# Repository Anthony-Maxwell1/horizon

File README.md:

# Horizon

## AI Usage

AI was used during the schematic stage, providing insight on component suggestions, finding some obscure docs and providing wiring/gpio usage suggestions. It was also used to review the schematic, in quick prototyping stage. It was also used quite heavily in understanding concepts such as decoupling, and pretty heavily in instructing on how to apply decoupling.

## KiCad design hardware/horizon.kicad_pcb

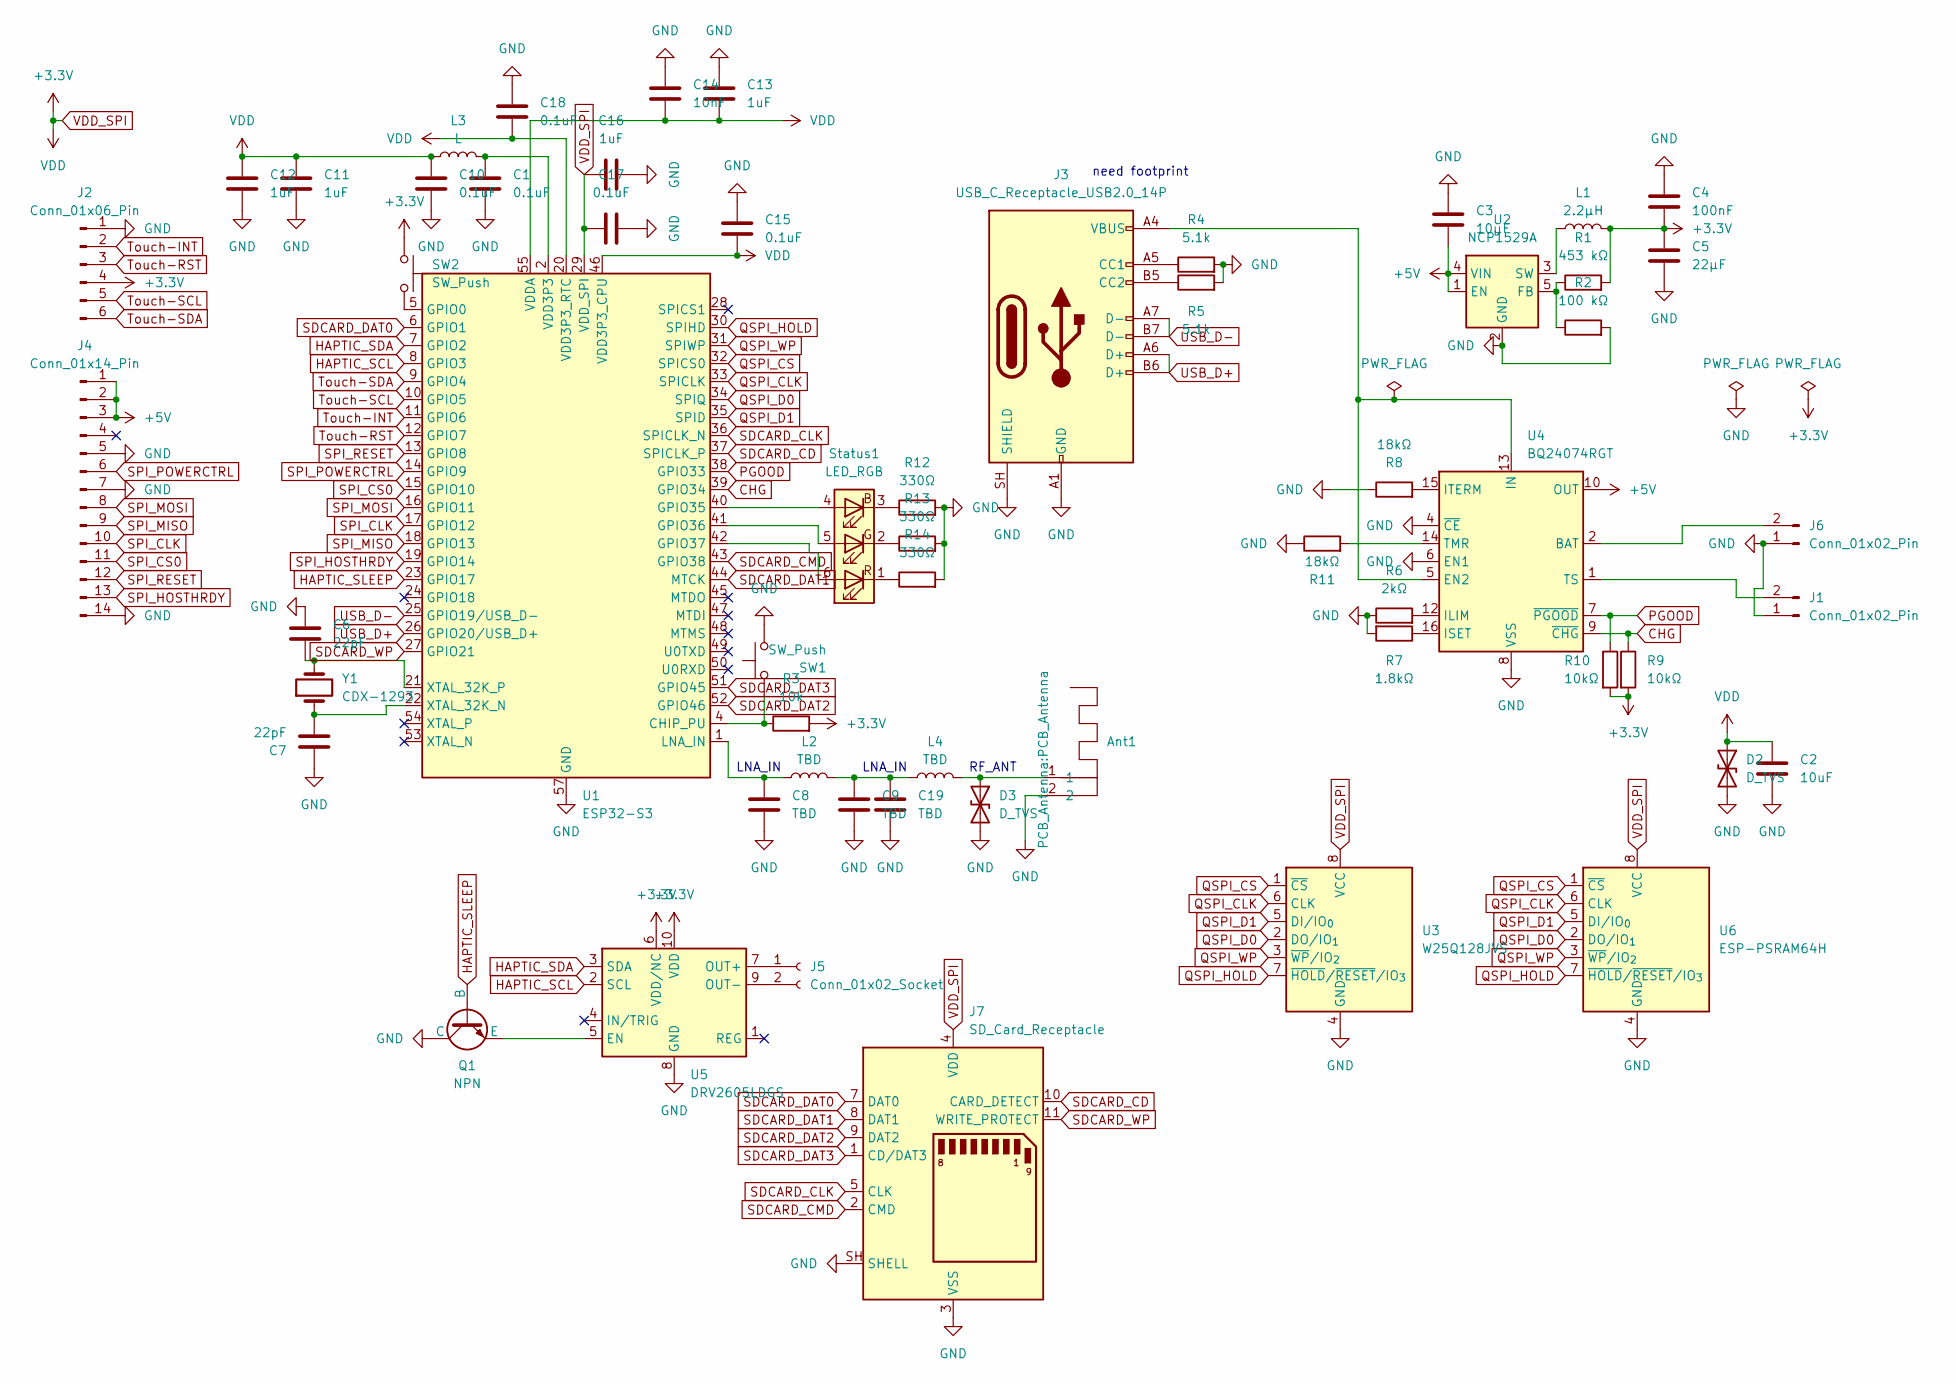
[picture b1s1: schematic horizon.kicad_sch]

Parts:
Ant1: PCB_Antenna:PCB_Antenna; PCB_Antenna
C1: 0.1uF; D_0402_1005Metric
C2: 10uF; C_0201_0603Metric
C3: 10µF; C_0201_0603Metric
C4: 100nF; C_0201_0603Metric
C5: 22µF; C_0201_0603Metric
C6, C7: 22pF; C_0201_0603Metric
C8, C9, C19: TBD; C_0201_0603Metric
C10, C15, C17, C18: 0.1uF; C_0201_0603Metric
C11, C12, C13, C16: 1uF; C_0201_0603Metric
C14: 10nF; C_0201_0603Metric
D2, D3: D_TVS; D_0402_1005Metric
J1, J6: Conn_01x02_Pin; JST_PH_S2B-PH-K_1x02_P2.00mm_Horizontal
J2: Conn_01x06_Pin; Hirose_FH12-6S-0.5SH_1x06-1MP_P0.50mm_Horizontal
J3: USB_C_Receptacle_USB2.0_14P; USB_C_Receptacle_HRO_TYPE-C-31-M-12
J4: Conn_01x14_Pin; Hirose_FH12-14S-0.5SH_1x14-1MP_P0.50mm_Horizontal
J5: Conn_01x02_Socket; 2x solder pads
J7: SD_Card_Receptacle; SD_TE_2041021
L1: 2.2µH; L_Bourns_SDR0604
L2, L4: TBD; L_Bourns_SDR0604
L3: L; L_Bourns_SDR0604
Q1: NPN; TO-92L
R1: 453 kΩ; R_0603_1608Metric
R2: 100 kΩ; R_0603_1608Metric
R3: 10k; R_0603_1608Metric
R4, R5: 5.1k; R_0603_1608Metric
R6: 2kΩ; R_0603_1608Metric
R7: 1.8kΩ; R_0603_1608Metric
R8, R11: 18kΩ; R_0603_1608Metric
R9, R10: 10kΩ; R_0603_1608Metric
R12, R13, R14: 330Ω; R_0603_1608Metric
SW1: SW_Push; SW_PUSH_6mm
SW2: SW_Push; SW_Push_1P2T_Vertical_E-Switch_800UDP8P1A1M6
Status1: LED_RGB; LED_RGB_5050-6
U1: ESP32-S3; QFN-56-1EP_7x7mm_P0.4mm_EP4x4mm
U2: NCP1529A; SOT-23-5
U3: W25Q128JVS; SOIC-8_5.3x5.3mm_P1.27mm
U4: BQ24074RGT; VQFN-16-1EP_3x3mm_P0.5mm_EP1.6x1.6mm
U5: DRV2605LDGS; TSSOP-10_3x3mm_P0.5mm
U6: ESP-PSRAM64H; SOIC-8_5.3x5.3mm_P1.27mm
Y1: CDX-1293; Crystal_SMD_3215-2Pin_3.2x1.5mm

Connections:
+5V: C3.1, J4.1, J4.2, J4.3, U2.1 (EN), U2.4 (VIN), U4.10 (OUT), U4.11 (OUT)
CHG: R9.1, U1.39 (GPIO34), U4.9 (~CHG)
GND: Ant1.2, C1.2, C2.2, C3.2, C4.2, C5.2, C6.2, C7.2, C8.2, C9.2, C10.2, C11.2, C12.2, C13.2, C14.2, C15.2, C16.2, C17.2, C18.2, C19.2, D2.2 (A2), D3.2 (A2), J1.1, J2.1, J3.A1 (GND), J3.A12 (GND), J3.B1 (GND), J3.B12 (GND), J3.SH (SHIELD), J4.5, J4.7, J4.14, J6.1, J7.3 (VSS), J7.6 (VSS), J7.SH (SHELL), Q1.1 (C), R2.2, R4.2, R5.2, R6.1, R7.2, R8.1, R11.1, R12.2, R13.2, R14.2, SW1.2, U1.57 (GND), U2.2 (GND), U3.4 (GND), U4.4 (~CE), U4.6 (EN1), U4.8 (VSS), U4.17 (VSS), U5.8 (GND), U6.4 (GND)
HAPTIC_SCL: U1.8 (GPIO3), U5.2 (SCL)
HAPTIC_SDA: U1.7 (GPIO2), U5.3 (SDA)
HAPTIC_SLEEP: Q1.2 (B), U1.23 (GPIO17)
unnamed: C1.1, L3.2, U1.2 (VDD3P3), U1.3 (VDD3P3)
unnamed: C9.1, C19.1, L2.2, L4.1
unnamed: Ant1.1, D3.1 (A1), L4.2
unnamed: J1.2, U4.1 (TS)
unnamed: J3.A5 (CC1), R4.1
unnamed: J3.B5 (CC2), R5.1
unnamed: J5.1, U5.7 (OUT+)
unnamed: J5.2, U5.9 (OUT-)
unnamed: J6.2, U4.2 (BAT), U4.3 (BAT)
unnamed: Q1.3 (E), U5.5 (EN)
unnamed: Status1.4 (BA), U1.40 (GPIO35)
unnamed: R12.1, Status1.3 (BK)
unnamed: Status1.5 (GA), U1.41 (GPIO36)
unnamed: R13.1, Status1.2 (GK)
unnamed: Status1.6 (RA), U1.42 (GPIO37)
unnamed: R14.1, Status1.1 (RK)
unnamed: R3.1, SW1.1, U1.4 (CHIP_PU)
unnamed: SW2.2, U1.5 (GPIO0)
unnamed: C8.1, L2.1, U1.1 (LNA_IN)
unnamed: C7.1, U1.22 (XTAL_32K_N), Y1.1
unnamed: C6.1, U1.21 (XTAL_32K_P), Y1.2
unnamed: R1.1, R2.1, U2.5 (FB)
unnamed: L1.1, U2.3 (SW)
unnamed: J3.A4 (VBUS), J3.A9 (VBUS), J3.B4 (VBUS), J3.B9 (VBUS), U4.5 (EN2), U4.13 (IN)
unnamed: R6.2, U4.12 (ILIM)
unnamed: R7.1, U4.16 (ISET)
unnamed: R8.2, U4.15 (ITERM)
unnamed: R11.2, U4.14 (TMR)
PGOOD: R10.1, U1.38 (GPIO33), U4.7 (~PGOOD)
QSPI_CLK: U1.33 (SPICLK), U3.6 (CLK), U6.6 (CLK)
QSPI_CS: U1.32 (SPICS0), U3.1 (~CS), U6.1 (~CS)
QSPI_D0: U1.34 (SPIQ), U3.2 (DO/IO_{1}), U6.2 (DO/IO_{1})
QSPI_D1: U1.35 (SPID), U3.5 (DI/IO_{0}), U6.5 (DI/IO_{0})
QSPI_HOLD: U1.30 (SPIHD), U3.7 (~HOLD/~RESET/IO_{3}), U6.7 (~HOLD/~RESET/IO_{3})
QSPI_WP: U1.31 (SPIWP), U3.3 (~WP/IO_{2}), U6.3 (~WP/IO_{2})
SDCARD_CD: J7.10 (CARD_DETECT), U1.37 (SPICLK_P)
SDCARD_CLK: J7.5 (CLK), U1.36 (SPICLK_N)
SDCARD_CMD: J7.2 (CMD), U1.43 (GPIO38)
SDCARD_DAT0: J7.7 (DAT0), U1.6 (GPIO1)
SDCARD_DAT1: J7.8 (DAT1), U1.44 (MTCK)
SDCARD_DAT2: J7.9 (DAT2), U1.52 (GPIO46)
SDCARD_DAT3: J7.1 (CD/DAT3), U1.51 (GPIO45)
SDCARD_WP: J7.11 (WRITE_PROTECT), U1.27 (GPIO21)
SPI_CLK: J4.10, U1.17 (GPIO12)
SPI_CS0: J4.11, U1.15 (GPIO10)
SPI_HOSTHRDY: J4.13, U1.19 (GPIO14)
SPI_MISO: J4.9, U1.18 (GPIO13)
SPI_MOSI: J4.8, U1.16 (GPIO11)
SPI_POWERCTRL: J4.6, U1.14 (GPIO9)
SPI_RESET: J4.12, U1.13 (GPIO8)
Touch-INT: J2.2, U1.11 (GPIO6)
Touch-RST: J2.3, U1.12 (GPIO7)
Touch-SCL: J2.5, U1.10 (GPIO5)
Touch-SDA: J2.6, U1.9 (GPIO4)
USB_D+: J3.A6 (D+), J3.B6 (D+), U1.26 (GPIO20/USB_D+)
USB_D-: J3.A7 (D-), J3.B7 (D-), U1.25 (GPIO19/USB_D-)
VDD_SPI: C2.1, C4.1, C5.1, C10.1, C11.1, C12.1, C13.1, C14.1, C15.1, C16.1, C17.1, C18.1, D2.1 (A1), J2.4, J7.4 (VDD), L1.2, L3.1, R1.2, R3.2, R9.2, R10.2, SW2.1, U1.20 (VDD3P3_RTC), U1.29 (VDD_SPI), U1.46 (VDD3P3_CPU), U1.55 (VDDA), U1.56 (VDDA), U3.8 (VCC), U5.6 (VDD/NC), U5.10 (VDD), U6.8 (VCC)

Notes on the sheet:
LNA_IN
need footprint
RF_ANT

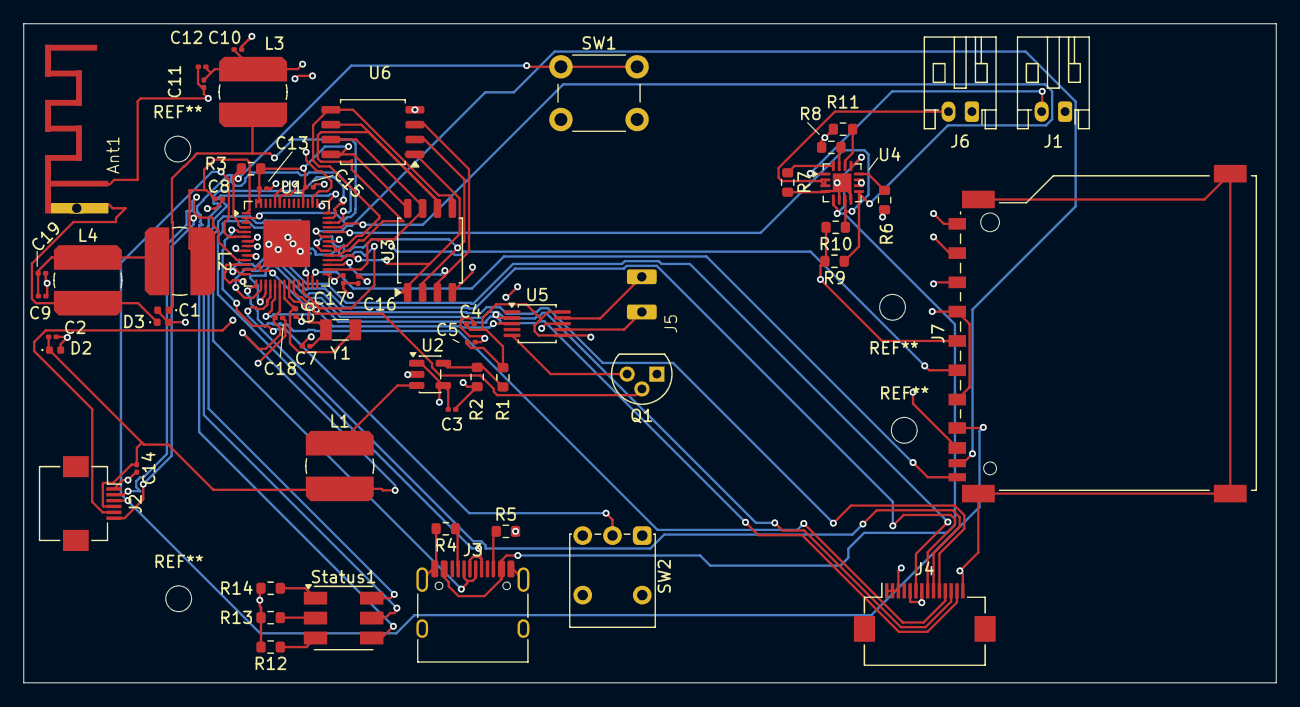
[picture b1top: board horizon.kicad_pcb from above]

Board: 4 copper layers, 106.9 x 56.2 mm, 58 parts (0 on the bottom side), 63 nets.

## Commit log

2026-05-10 Working on PD and QSPI
2026-05-11 Remove kicad history folder
2026-05-11 Working on schematic
2026-05-11 Finished schematic draft
2026-05-11 Added touch I2C and working on adding driver for LVGL
2026-05-12 Added journal
2026-05-12 Finalising schematic
2026-05-12 Finished schematic and began work on PCB
2026-05-13 Added lvgl config
2026-05-13 Added quick example from online
2026-05-13 added antenna
2026-05-13 Finished prototype pcb
2026-05-13 Added haptic and sleep button
2026-05-14 Redoing pcb and fixed schem
2026-05-15 Finished pcb!
2026-05-15 Fixed keepout on antenna
2026-05-15 Adding SD card slot
2026-05-15 Finished SD card wiring
2026-05-16 Fixed connectors
2026-05-16 Working on native drivers
2026-05-17 replaced timer for desktop
2026-05-18 Added PSRAM fr this time, and got it to compile
2026-05-19 Removed build flags that did nothing new but added a lot of warnings
2026-05-19 some changes
2026-05-20 Finished native platform code, working on platform-agnostic code
2026-05-21 Working on reading page
2026-05-21 Fixed binary search alongside other changes
2026-05-21 Cleaned up debug printf's from last commit
2026-05-22 Working on book drawer
2026-05-22 trying to get the touch to work properly
2026-05-22 trying to get the touch to work properly try 2 git sucks
2026-05-22 fixed touch
2026-05-22 reverted to proper reading page
2026-05-22 Fixing wifi
2026-05-22 Added script to copy dlls in for windows for convenience
2026-05-23 added metadata
2026-05-23 Working on battery widget
2026-05-23 Completed config and some widgets
2026-05-24 Added book_Drawer to config
2026-05-25 Removed fluff
